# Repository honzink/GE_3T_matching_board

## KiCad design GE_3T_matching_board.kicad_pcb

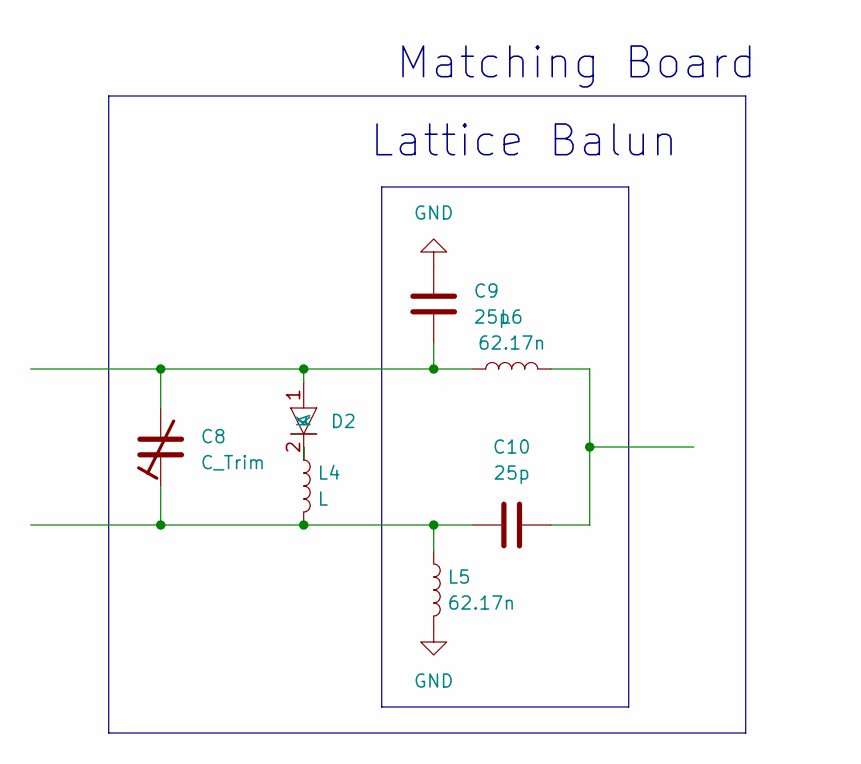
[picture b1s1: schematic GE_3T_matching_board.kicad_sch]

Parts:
C8: C_Trim; CAP_1111_HIQ_KNO
C9, C10: 25p; CAP_1111_HIQ_KNO
D2: PIN_diode_NonMagnetic_HighPower
L4: L; CAP_1111_HIQ_KNO
L5, L6: 62.17n; CAP_1111_HIQ_KNO

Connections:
GND: C9.1, L5.2
unnamed: C8.1, C10.1, L4.2, L5.1
unnamed: C10.2, L6.2
unnamed: C8.2, C9.2, D2.1 (A), L6.1
unnamed: D2.2 (K), L4.1

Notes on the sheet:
Lattice Balun
Matching Board

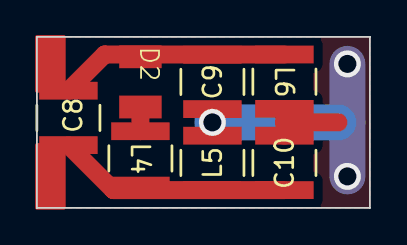
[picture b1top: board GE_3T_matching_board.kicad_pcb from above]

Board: 2 copper layers, 18.5 x 9.5 mm, 7 parts (0 on the bottom side), 5 nets.

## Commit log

2023-11-25 created schematic
2023-11-30 send to Nibardo to check
2023-12-05 smaller ground plane
2023-12-06 added solder paste for coil terminals, smaller bottom copper
2023-12-07 manufactured at PCBway, fixed issue
